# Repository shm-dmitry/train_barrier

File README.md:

It's a toy for a children :)
I assembled board, its worked.
Known issues:
- schematics/board. I know how to make it better. But current design ok for a toy. I will chabnge it in case of child requested new version :)
- 3D model: train-barrier-cap. But I printed it 5 times, and last version was acceptable, so maybe I will change it later.
- firmware: There are some issue with beeper, I will check it.

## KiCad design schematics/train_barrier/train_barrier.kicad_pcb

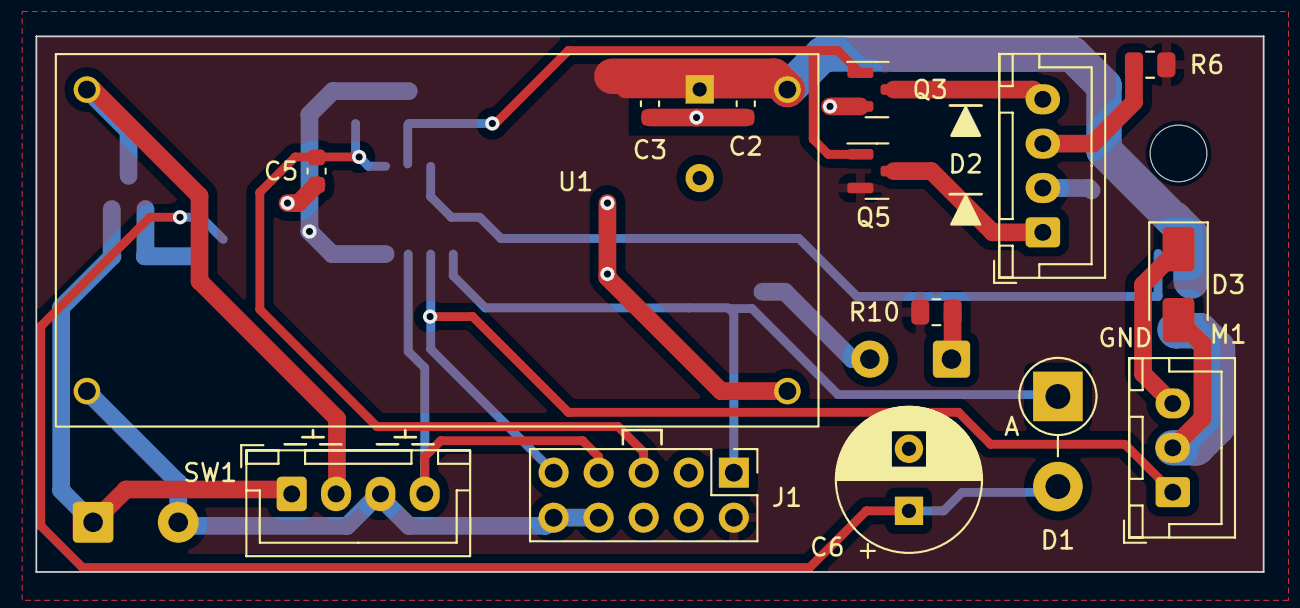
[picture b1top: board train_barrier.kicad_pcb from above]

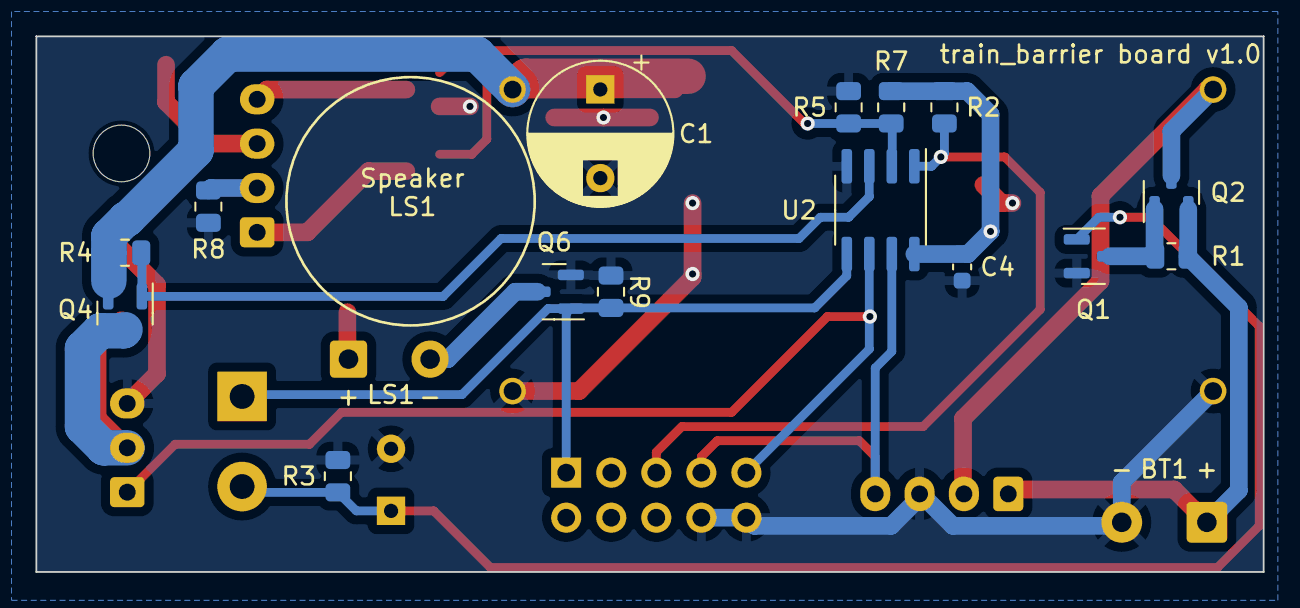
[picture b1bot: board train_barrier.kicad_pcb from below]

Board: 2 copper layers, 69.2 x 30.2 mm, 33 parts (17 on the bottom side), 19 nets.

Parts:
BT1: 9V; SolderWire-0.5sqmm_1x02_P4.8mm_D0.9mm_OD2.3mm
C1: 1000 uF; CP_Radial_D8.0mm_P5.00mm
C2: 22 uF; C_0603_1608Metric
C3, C4, C5: 0.1 uF; C_0603_1608Metric
C6: 22 uF; CP_Radial_D8.0mm_P3.50mm
D1: DIODE; D_5W_P5.08mm_Vertical_AnodeUp
D2: LED_Dual_AKAK; JST_XH_B4B-XH-A_1x04_P2.50mm_Vertical
D3: SMAJ5.0CA-TR; D_SMA
H1: MountingHole; MountingHole_3.2mm_M3
J1: USBASP; PinHeader_2x05_P2.54mm_Vertical
LS1: Speaker_Crystal; SolderWire-0.5sqmm_1x02_P4.6mm_D0.9mm_OD2.1mm
M1: Motor_Servo; JST_XH_B3B-XH-A_1x03_P2.50mm_Vertical
Q1, Q3, Q6: IRLML0030; SOT-23
Q2, Q4, Q5: IRLML5203; SOT-23
R1, R4, R5, R7, R9: 300K; R_0805_2012Metric
R2: 10K; R_0805_2012Metric
R3: 100K; R_0805_2012Metric
R6, R8: 100; R_0805_2012Metric
R10: 0; R_0805_2012Metric
SW1: SW_Push_Dual_x2; JST_XH_B4B-XH-A_1x04_P2.50mm_Vertical
U1: LM2596S; DCDC_LM2596
U2: ATtiny13A-SS; SOIC-8_3.9x4.9mm_P1.27mm

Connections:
+5V: C1.1, C2.1, C3.1, C4.1, J1.2, Q4.2 (S), Q5.2 (S), R2.2, R4.2, R6.1, R7.2, R10.1, U1.4 (OUT_VCC), U2.8 (VCC)
BUTTON: J1.7, SW1.4 (D), U2.7 (PB2)
GND: BT1.2 (-), C1.2, C2.2, C3.2, C4.2, C5.2, C6.2, D3.1 (A1), J1.8, J1.10, M1.3 (-), Q1.2 (S), Q3.2 (S), Q6.2 (S), R3.1, R5.2, R8.2, R9.2, SW1.3 (C), U1.2 (IN_GND), U1.3 (OUT_GND), U2.4 (GND)
LED: Q3.1 (G), Q5.1 (G), R5.1, R7.1, U2.2 (PB3)
NOISE: D1.1 (K), J1.1, Q6.1 (G), R9.1, U2.5 (PB0)
unnamed: BT1.1 (+), Q2.2 (S), R1.2, SW1.1 (C)
unnamed: D2.1 (A1), Q5.3 (D)
unnamed: D2.2 (K1), R8.1
unnamed: D2.3 (A2), R6.2
unnamed: D2.4 (K2), Q3.3 (D)
unnamed: D3.2 (A2), M1.2 (+), Q4.3 (D)
unnamed: LS1.1, R10.2
unnamed: LS1.2, Q6.3 (D)
unnamed: Q1.3 (D), Q2.1 (G), R1.1
unnamed: Q2.3 (D), SW1.2 (D), U1.1 (IN_VCC)
PWR_EN: C6.1, D1.2 (A), Q1.1 (G), R3.2
RESET: C5.1, J1.5, R2.1, U2.1 (~RESET/PB5)
SERVO_EN: Q4.1 (G), R4.1, U2.3 (PB4)
SERVO_PWM: J1.9, M1.1 (PWM), U2.6 (PB1)

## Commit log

2023-03-22 it's worked
